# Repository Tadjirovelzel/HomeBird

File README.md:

The project NestWacht in collaboration with the TU Delft and other benefactors aims to design a sensor station in the form of a birdhouse that uses a camera and weather sensors to document bird activity and monitor properties of the local atmosphere such as humidity, pressure and particulate matter levels. 
This file serves to outline the structure and purpose of the folders contained within the project.

# Project Structure
The essential project structure is displayed below:

    -Code
        -arduino_firmware
        -esp_firmware
        -test_camera
        -test_video
        -legacy_code
    -Enclosure
    -Kicad
        -main_board
        -camera_board
        -gerbers

    The project also contains the complete material bill and the login information for the Node Developer platform.
    Some irrelevant and older development code is stored in the legacy_code folder. 

The electronical components were initally designed by Maarten van Schagen and Quinten Luyten. Tadjiro Velzel further implemented the design and attempted to correct inital mistakes.
The programming necessary to ensure correct and smooth operation of the board and the server was done by Lennard Duynkerke.
The enclosure of the electronics was designed by Thomas van Leeuwen.
The project was overseen and managed by Marit Bogert and Teun Verkerk.

# Hardware
The main board contains the following components, split into sections.

    Power systems section:
        - Three battery connector footprints that lead to battery holders containing three 16650 LiOn batteries
        - Three TP4056 battery charger modules
        - A Solar charger footprint leading to a solar panel
        - A boost converter that regulates the battery power to 5V
        - A Diode to route solar power directly to the boost converter
        - A Diode to regulate the arduino's ability to turn off the boost converter, thus turning off the Esp32 and particulate matter sensor
        - A power FET which turns off the Esp32 and Particulate matter sensor
        - Resistors to regulate the power throughput towards the FET

    Computative section:
        - An Arduino Every that drives the power towards the ESP32 and operates the sensors and an SD card to store sensor data.
        - A LilyGo ESP32 development board

    Sensoric section:
        - Two BME280 breakout boards to monitor air pressure, humidity and temperature both within the birdhouse and towards the outside air
        - A PMS5003 particulate matter sensor

    Data transfer:
        - A Sim LTE module (LilyGo SIM7600E) for data transfer
        - An LTE antenna to transfer data over LTE
        - A Sim-card to route information accross the internet
        - An SD card that stores the sensor data before sending it

The Camera Board contains the following components:

    - An OV2640 camera operating within the visible and infrared spectra 
    - A 24 pin camera connector, soldered to the board
    - A network of capacitors to smooth the voltages of the camera connector and voltage regulators
    - A 2.8V and 1.2V voltage regulator to supply the camera
    - A system of resistors to preload the camera
    - A motion sensor to detect bird activity and trigger the camera
    - Four infrared LEDs to light up for pictures at night, which the birds cannot sense
    - A larger resistor to regulate current to the infrared LEDs

To contain the electronics mentioned above, a plastic enclosure made, printed in PETG by 3d-printer. The design files for this are available in the enclosure folder.

# Software
The software is split in two parts: `arduino_firmware` and `esp_firmware`. The former is designed for the Arduino Every, the main computational unit which is always powered on and operates sensors, sd card, and power to the ESP32. The latter is ran on the LilyGo ESP32 and is used to communicate with the outer world over a 4G connection, as well as to take pictures with the OV2640 camera. Two test files are added in order to test a specific part of the software, `test_camera` to test the camera either over WiFi or over 4G and `test_video` to record an .avi video by sticking individual .jpg files together. For a more detailed description of the software one is directed to the headers of the individual .cpp files.

# Problems
Currently the project contains the following issues:
* Sim module will not send large pictures
* Camera init and capture is inconsistent, bound to inconsistency of the camera connector
* Pin assignment in code does not correspond to PCB design files: PCB files are incorrect and can never work: pin assignment in software is correct.
* Complete integration was never tested
* Likely complete system is too power intensive to drive by solar panel. (Also never tested fully)

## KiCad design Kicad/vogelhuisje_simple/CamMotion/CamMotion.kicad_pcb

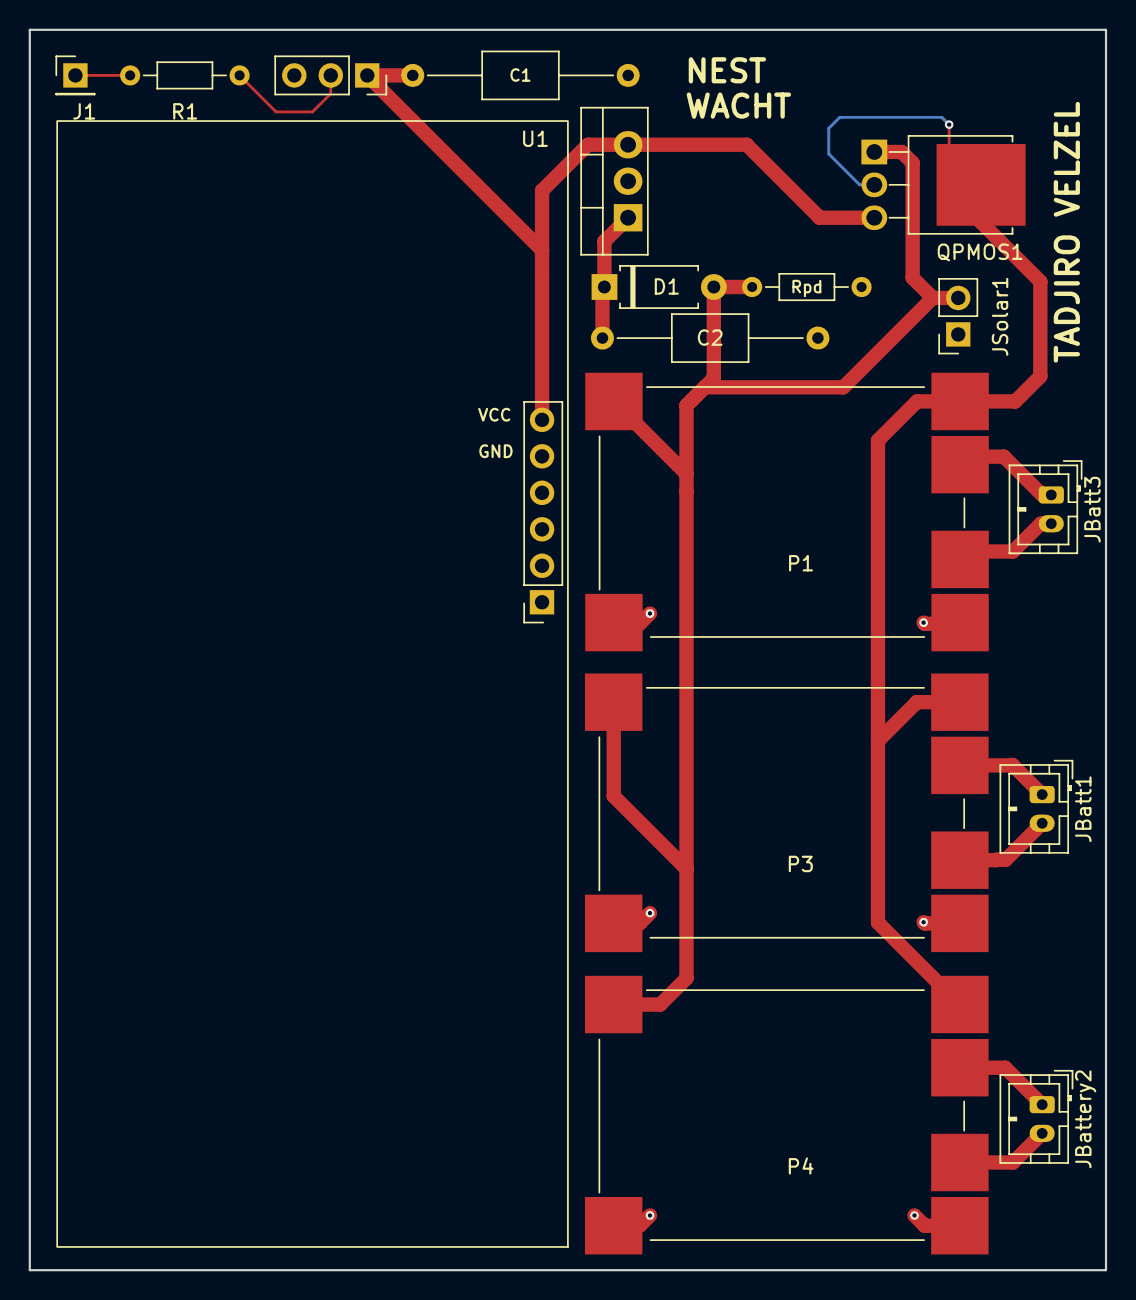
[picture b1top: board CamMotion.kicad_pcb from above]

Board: 2 copper layers, 74.9 x 86.4 mm, 17 parts (0 on the bottom side), 13 nets.

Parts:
C1: 100u; C_Axial_L5.1mm_D3.1mm_P15.00mm_Horizontal
C2: 10u; C_Axial_L5.1mm_D3.1mm_P15.00mm_Horizontal
D1: D_Schot; D_A-405_P7.62mm_Horizontal
J1: Conn_01x01_Pin; PinHeader_1x01_P2.54mm_Vertical
JBatt1: Batt3; JST_PH_B2B-PH-K_1x02_P2.00mm_Vertical
JBatt3: Batt1; JST_PH_B2B-PH-K_1x02_P2.00mm_Vertical
JBattery2: JBatt2; JST_PH_B2B-PH-K_1x02_P2.00mm_Vertical
JMotion1: -; PinSocket_1x03_P2.54mm_Vertical
JSolar1: Conn_01x02_Female; PinSocket_1x02_P2.54mm_Vertical
P1, P3, P4: TP4056breakout
QPMOS1: TSM680P06CH
R1: 4.7k; R_Axial_DIN0204_L3.6mm_D1.6mm_P7.62mm_Horizontal
Rpd: 47k; R_Axial_DIN0204_L3.6mm_D1.6mm_P7.62mm_Horizontal
U1: T-simcam; TSimCam
UReg1: LD1117; TO-220-3_Vertical

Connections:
/Power Supply/VSolar: D1.2 (A), JSolar1.2, P1.1 (Vin+), P3.1 (Vin+), P4.1 (Vin+), QPMOS1.1 (G), Rpd.2
/Power Supply/Vbat: P1.3 (OUT+), P3.3 (OUT+), P4.3 (OUT+), QPMOS1.2 (D)
/Sensors and microcontrollers/Motion_out: J1.1, R1.1
GND: C1.2, C2.2, JMotion1.3, JSolar1.1, P1.2 (GND), P1.6 (OUT-), P3.2 (GND), P3.6 (OUT-), P4.2 (GND), P4.6 (OUT-), Rpd.1, U1.5 (Gnd), UReg1.2 (GND)
unnamed: C2.1, D1.1 (K), UReg1.1 (VI)
unnamed: JBatt1.1, P3.4 (B+)
unnamed: JBatt1.2, P3.5 (B-)
unnamed: JBatt3.1, P1.4 (B+)
unnamed: JBatt3.2, P1.5 (B-)
unnamed: JBattery2.1, P4.4 (B+)
unnamed: JBattery2.2, P4.5 (B-)
unnamed: JMotion1.2, R1.2
Vcc: C1.1, JMotion1.1, QPMOS1.3 (S), U1.6 (3V3), UReg1.3 (VO)

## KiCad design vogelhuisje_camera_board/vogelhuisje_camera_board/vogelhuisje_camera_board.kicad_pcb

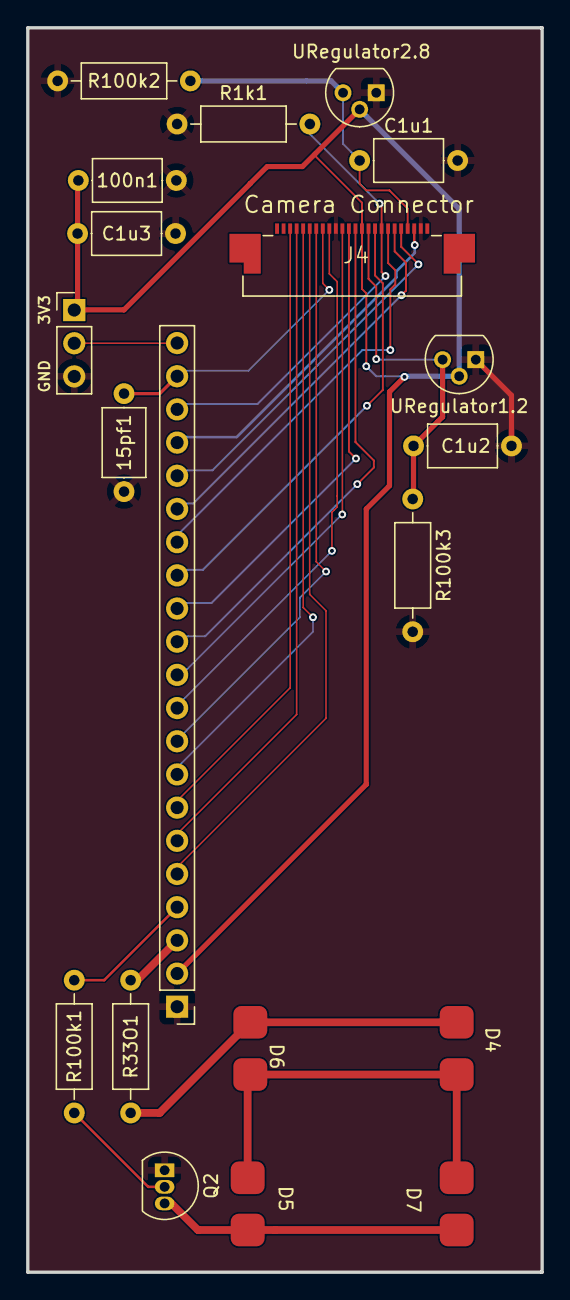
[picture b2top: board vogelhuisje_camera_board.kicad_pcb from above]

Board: 2 copper layers, 39.4 x 95.2 mm, 20 parts (0 on the bottom side), 27 nets.

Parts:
15pf1: 15pF; C_Axial_L5.1mm_D3.1mm_P7.50mm_Horizontal
100n1: 100nF; C_Axial_L5.1mm_D3.1mm_P7.50mm_Horizontal
C1u1, C1u2, C1u3: 1u; C_Axial_L5.1mm_D3.1mm_P7.50mm_Horizontal
D4, D5, D6, D7: LED; SFH 4253
J1: Conn_01x21_Female; PinHeader_1x21_P2.54mm_Vertical
J4: Camera Connector; CONN_MOLEX_52437-2471
JMotion1: Conn_01x03_Female; PinHeader_1x03_P2.54mm_Vertical
Q2: Q_NMOS_DGS; TO-92L_Inline
R1k1: 1k1; R_Axial_DIN0207_L6.3mm_D2.5mm_P10.16mm_Horizontal
R33O1: 33Ohm; R_Axial_DIN0207_L6.3mm_D2.5mm_P10.16mm_Horizontal
R100k1, R100k2, R100k3: 100kOhm; R_Axial_DIN0207_L6.3mm_D2.5mm_P10.16mm_Horizontal
URegulator1.2: 1.2V Regulator; TO-92
URegulator2.8: 2.8V regulator; TO-92

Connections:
3V3: 100n1.2, C1u3.1, J1.2, J4.14, JMotion1.1, URegulator1.2.2 (VI), URegulator2.8.2 (VI)
/Camera Module/CAM_RST: J1.16, J4.19
/Camera Module/CSI_D0: J1.5, J4.6
/Camera Module/CSI_D1: J1.6, J4.4
/Camera Module/CSI_D2: J1.7, J4.3
/Camera Module/CSI_D3: J1.8, J4.5
/Camera Module/CSI_D4: J1.9, J4.7
/Camera Module/CSI_D5: J1.10, J4.9
/Camera Module/CSI_D6: J1.11, J4.11
/Camera Module/CSI_D7: J1.12, J4.13
/Camera Module/CSI_HSYNC: J1.14, J4.16
/Camera Module/CSI_MCLK: J1.13, J4.12
/Camera Module/CSI_PCLK: 15pf1.2, J1.20, J4.8
/Camera Module/CSI_VSYNC: J1.15, J4.18
/Camera Module/Motion_out: J1.21, JMotion1.2
/Camera Module/PWDN: J1.19, J4.17, R1k1.2
/Camera Module/TWI_SCK: J1.17, J4.20
/Camera Module/TWI_SDA: J1.18, J4.22
/Camera Module/V_led_switch-: J1.4, R100k1.1
/Camera Module/Vbat: J1.3, R33O1.1
CSI_1.2V: C1u2.1, J4.15, R100k3.1, URegulator1.2.3 (VO)
CSI_2.8V: C1u1.1, J4.21, R100k2.1, URegulator2.8.3 (VO)
GND: 15pf1.1, 100n1.1, C1u1.2, C1u2.2, C1u3.2, J1.1, J4.10, J4.23, JMotion1.3, Q2.1 (D), R1k1.1, R100k2.2, R100k3.2, URegulator1.2.1 (GND), URegulator2.8.1 (GND)
unnamed: D4.1 (K), D5.2 (A), D6.1 (K), D7.2 (A)
unnamed: D4.2 (A), D6.2 (A), R33O1.2
unnamed: D5.1 (K), D7.1 (K), Q2.3 (S)
unnamed: Q2.2 (G), R100k1.2

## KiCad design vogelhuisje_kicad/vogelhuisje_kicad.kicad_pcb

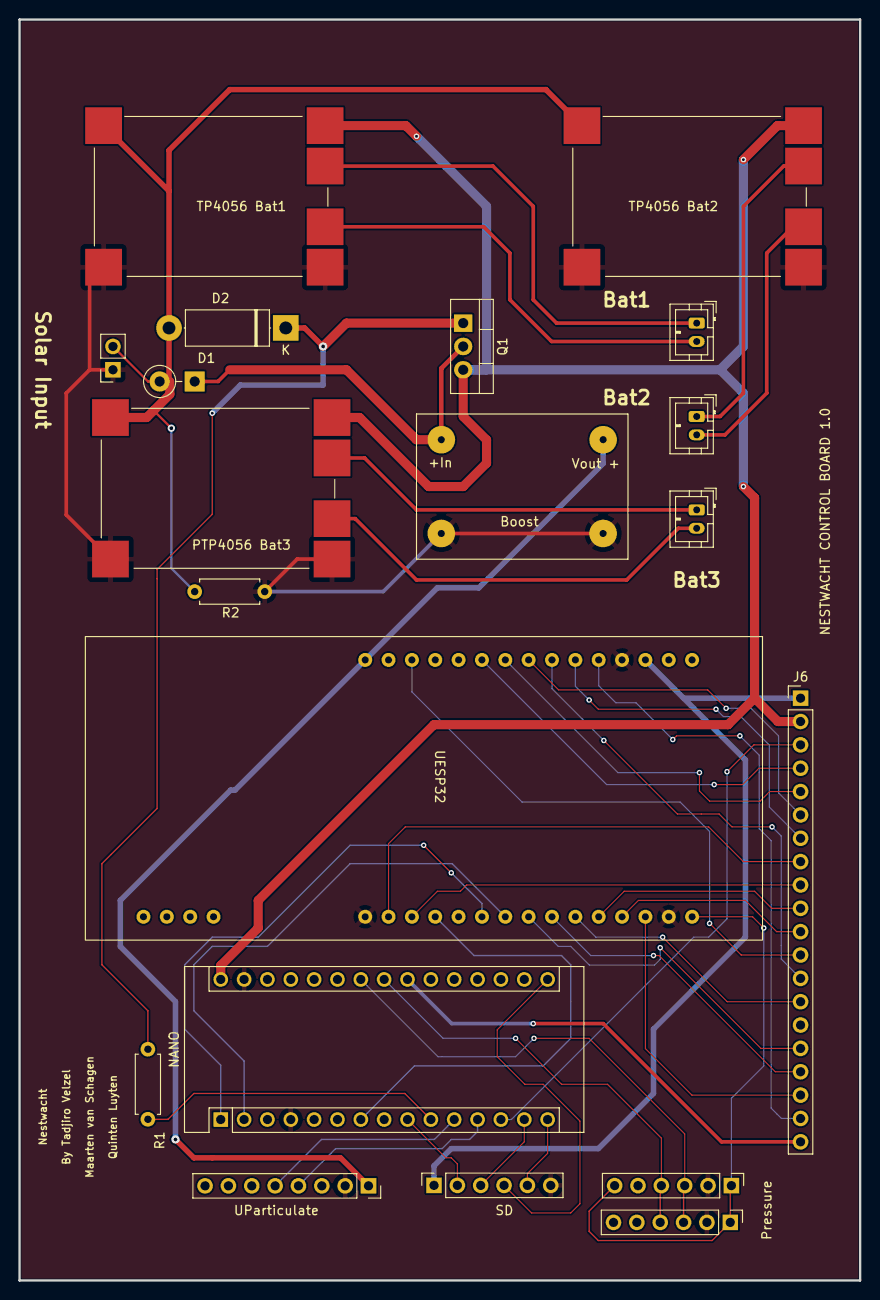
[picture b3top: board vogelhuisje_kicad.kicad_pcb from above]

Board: 2 copper layers, 91.4 x 137.2 mm, 20 parts (0 on the bottom side), 43 nets.

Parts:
Boost: GenericBoostConverter
D1: D_Schottky; D_DO-41_SOD81_P3.81mm_Vertical_KathodeUp
D2: D; D_5W_P12.70mm_Horizontal
J6: Conn_01x20_Female; PinHeader_1x20_P2.54mm_Vertical
JBatt1: Batt3; JST_PH_B2B-PH-K_1x02_P2.00mm_Vertical
JBatt3: Batt1; JST_PH_B2B-PH-K_1x02_P2.00mm_Vertical
JBattery2: JBatt2; JST_PH_B2B-PH-K_1x02_P2.00mm_Vertical
JSolar1: Conn_01x02_Female; PinSocket_1x02_P2.54mm_Vertical
NANO: Arduino_Nano_v3.x; Arduino_Nano
PTP4056 Bat3: TP4056breakout
Pressure: BME280Breakout; PinHeader_1x06_P2.54mm_Vertical
Q1: Q_PMOS_GSD; TO-220-3_Vertical
R1: -; R_Axial_DIN0207_L6.3mm_D2.5mm_P7.62mm_Horizontal
R2: 100k; R_Axial_DIN0207_L6.3mm_D2.5mm_P7.62mm_Horizontal
SD: SD-card-reader; PinSocket_1x06_P2.54mm_Vertical
TP4056 Bat1, TP4056 Bat2: TP4056breakout
U6: BME280Breakout; PinHeader_1x06_P2.54mm_Vertical
UESP32: ESP32-LilyGo-T_PCIE; Lilygo_T_PCIE
UParticulate: PMS5003; PinSocket_1x08_P2.54mm_Vertical

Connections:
+3V3: J6.1, SD.1 (3V3), UESP32.3 (3V3)
+5V: Boost.3 (Vout+), UESP32.15 (5V-in), UParticulate.1 (VCC)
/Power Supply/Vbat: J6.2, NANO.30 (VIN), PTP4056 Bat3.3 (OUT+), Q1.3 (D), TP4056 Bat1.3 (OUT+), TP4056 Bat2.3 (OUT+)
/Sensors and microcontrollers/BOOST: NANO.10 (D7), R1.1
/Sensors and microcontrollers/CLK: NANO.16 (D13), SD.4 (CLK)
/Sensors and microcontrollers/CS_SD: NANO.9 (D6), SD.2 (CS)
/Sensors and microcontrollers/HREF_CAM: J6.13, UESP32.7 (23)
/Sensors and microcontrollers/INT_OUT_ARD: NANO.7 (D4), UESP32.27 (2)
/Sensors and microcontrollers/LED_EN: J6.3, NANO.13 (D10)
/Sensors and microcontrollers/MISO: NANO.15 (D12), SD.5 (MISO)
/Sensors and microcontrollers/MOSI: NANO.14 (D11), SD.3 (MOSI)
/Sensors and microcontrollers/Motion_out: J6.20, NANO.22 (A3)
/Sensors and microcontrollers/PCLK_CAM: J6.19, UESP32.5 (22)
/Sensors and microcontrollers/PWDN_CAM: J6.18, UESP32.18 (32)
/Sensors and microcontrollers/RX_ARD: NANO.2 (D0/RX), UESP32.24 (4)
/Sensors and microcontrollers/RX_PMS: NANO.12 (D9), UParticulate.4 (RX)
/Sensors and microcontrollers/SCL: NANO.24 (A5), Pressure.3 (SCL), U6.3 (SCL)
/Sensors and microcontrollers/SDA: NANO.23 (A4), Pressure.4 (SDA), U6.4 (SDA)
/Sensors and microcontrollers/SIOD_CAM: J6.17, UESP32.22 (26)
/Sensors and microcontrollers/SOIC_CAM: J6.16, UESP32.23 (27)
/Sensors and microcontrollers/TX_ARD: NANO.1 (D1/TX), UESP32.25 (14)
/Sensors and microcontrollers/TX_PMS: NANO.11 (D8), UParticulate.5 (TX)
/Sensors and microcontrollers/VSYNC_CAM: J6.14, UESP32.21 (25)
/Sensors and microcontrollers/XCLK_CAM: J6.12, UESP32.13 (0)
/Sensors and microcontrollers/Y2_CAM: J6.4, UESP32.10 (5)
/Sensors and microcontrollers/Y3_CAM: J6.5, UESP32.9 (18)
/Sensors and microcontrollers/Y4_CAM: J6.6, UESP32.8 (19)
/Sensors and microcontrollers/Y5_CAM: J6.7, UESP32.6 (21)
/Sensors and microcontrollers/Y6_CAM: J6.8, UESP32.29 (15)
/Sensors and microcontrollers/Y7_CAM: J6.9, UESP32.28 (13)
/Sensors and microcontrollers/Y8_CAM: J6.10, UESP32.20 (34)
/Sensors and microcontrollers/Y9_CAM: J6.11, UESP32.19 (33)
GND: Boost.2 (GND), Boost.4 (GND), JSolar1.1, NANO.4 (GND), NANO.29 (GND), PTP4056 Bat3.2 (GND), PTP4056 Bat3.6 (OUT-), Pressure.2 (GND), R2.2, SD.6 (GND), TP4056 Bat1.2 (GND), TP4056 Bat1.6 (OUT-), TP4056 Bat2.2 (GND), TP4056 Bat2.6 (OUT-), U6.2 (GND), UESP32.4 (GND), UESP32.17 (GND), UESP32.30 (GND), UParticulate.2 (GND)
unnamed: Boost.1 (Vin+), D1.1 (K), Q1.2 (S)
unnamed: D1.2 (A), D2.2 (A), JSolar1.2, PTP4056 Bat3.1 (Vin+), R2.1, TP4056 Bat1.1 (Vin+), TP4056 Bat2.1 (Vin+)
unnamed: D2.1 (K), Q1.1 (G), R1.2
unnamed: JBatt1.1, TP4056 Bat2.4 (B+)
unnamed: JBatt1.2, TP4056 Bat2.5 (B-)
unnamed: JBatt3.1, PTP4056 Bat3.4 (B+)
unnamed: JBatt3.2, PTP4056 Bat3.5 (B-)
unnamed: JBattery2.1, TP4056 Bat1.4 (B+)
unnamed: JBattery2.2, TP4056 Bat1.5 (B-)
unnamed: Pressure.1 (Vcc), Pressure.6 (SDO), U6.1 (Vcc), UESP32.16 (3V3)

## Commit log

2022-01-31 [Hit return to continue]
2022-01-31 added wifi configuration
2022-02-23 added PMS5003 and LowPower
2022-03-06 got powerdown working reliably!
2022-03-06 working on humidity
2022-03-13 worked on including time in data
2022-03-19 fixed time, and added testing camera code
2022-04-23 KiCad project
2022-04-23 Update ESP_arduino.sch-bak, Power_supply.sch, and 25 more files...
2022-04-23 Update ESP_arduino.sch, Power_supply.sch, and 5 more files...
2022-04-23 sim card support
2022-04-28 Add Camera to schematic
2022-04-29 Update Camera_module.sch, Camera_module.sch-bak, and 5 more files...
2022-06-25 PCB design
2022-07-04 PCB done with version 1
2022-07-04 fixed gerber file export
2022-07-04 saved file
2022-11-13 Kicad Changes Tadjiro
    Board now supports 3 lipo cells and a motion sensor.
2022-12-06 1st prototype
2022-12-28 camera test code
2023-01-04 Updated Camera Board
    Moved capacitors close to LDO output, corrected capacitor values and ported ground from the main board.
2023-01-04 Update main board
    Ground port added to connector
2023-01-14 debug sim7600
2023-01-28 Update arduino_firmware
2023-01-28 Update test_camera
2023-02-03 Old changes reuploaded
    Weird thing happened with git pushes. Hopefully this will solve the problems
2023-02-03 Gevecht met gerbers
    The gerber files put up a fight but at the end of the day I was able to make them work.
2023-02-17 changed camera connector, and updated regulator pins
2023-02-17 forgot to save
2023-02-17 again...
2023-02-24 updated to use new connector footprint
2023-03-06 test_camera PSRAM enabled
2023-03-08 Got a bunch of stuff working
2023-03-08 got a lot working
2023-03-10 Camera seems to be working now. MQTT doesn't.
2023-04-06 test_video
    Code to record avi-video and save to SD card
2023-04-06 Add function c_read_file
    Function to read file from SD card or SPIFFS to a buffer in order to be able to send the data over mqtt
2023-08-07 test_camera sim/wifi
    Split test_camera main.cpp in two files: main_sim.cpp and main_wifi.cpp
2023-08-07 Login instructions
2023-08-09 Clean up code
2023-08-28 Pin reassignment
2023-09-01 Structure change
    File structure change to cleanup KiCad Files
2023-09-01 Update sim.cpp and create global README
2023-09-01 Documentation & Structure
    Major restructuring and documentation update.
2023-09-02 Clean up code and add descriptive header to all .cpp code
2023-09-02 Enhance style of README.md
2023-10-25 FIles for T-SIMCAM
2023-11-16 New Ideas on http
2023-11-16 New push with http
2023-11-16 http push
2023-11-16 T-SIMCAM successful upload
2023-11-16 POST working over sim
2023-11-30 Github fixen, update vandaag
2023-12-01 Added printstatements, added files *_lib
    Print statements to find errors
    Added extra *_lib files doing the same thing as inspiration
    Right now the request fails after sending a few chuncks (usually 3)
2023-12-04 Small edits T-SIMCAM-FACTORY, upload new C++ code T-SIMCAM
2024-04-28 Push Simplified
2024-05-01 Finish pcb simplified
2024-05-05 Finished PCB
    Now more properly routed
